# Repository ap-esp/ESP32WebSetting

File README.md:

# Proyecto: ESP32WebSetting

_(Servidor web) administra el ESP32 DeviceIoT_

## Documentación en general

* [Url de Udemy](https://www.udemy.com/course/esp32websetting/learn/lecture/38215070?start=15#content) - Para acceder al curso de Udemy _Tener en cuenta que se necesitan **credenciales**
* [Instalaciones necesarias/recomendadas para el curso](./primeras_secciones/doc/Instalaciones+necesarias+y+complementarias.txt)- *Archivo descargado del curso*

### Enlaces de youtube

*[Primer vìdeo](URL)- *Descripción*  
*[Primer vìdeo](URL)- *Descripción*  
*[Primer vìdeo](URL)- *Descripción*  
*[Primer vìdeo](URL)- *Descripción*  
*[Primer vìdeo](URL)- *Descripción*  
*[Primer vìdeo](URL)- *Descripción*  
*[Primer vìdeo](URL)- *Descripción*  

## Comenzando 🚀

_Estas instrucciones te permitirán obtener una copia del proyecto en funcionamiento en tu máquina local para propósitos de desarrollo y pruebas._

Mira **Deployment** para conocer como desplegar el proyecto.

### Pre-requisitos 📋

* [Hardware](https://www.youtube.com/watch?v=RRcEQ5YeemU) Tutorial de cómo generar el archivo BOM desde KiCAD para realizar los PCB en JLCPCB
* [Caja plàstica](https://es.aliexpress.com/item/1005004092665115.html?spm=a2g0o.order_list.order_list_main.31.6dd5194d1SaNCY&gatewayAdapt=glo2esp) Caja de proyecto electrónico de Riel din, caja de conexiones de plástico ABS de 115x90x40mm, carcasa para PCB.
* [DIAGRAMA ESP32 DEVKIT](./primeras_secciones/doc/DIAGRAMA+ESP32+DEVKIT.pptx) Esquema bàsico de conexiones
* [Esquema y proyecto en KidCad](/home/arch/Escritorio/2024/ESP/ap-esp/ESP32WebSetting/primeras_secciones/doc/esp32_pro_relay/) Toda la informción y acrhivos del proyecto de **KidCAD**

### Instalación 🔧

_Una serie de ejemplos paso a paso que te dice lo que debes ejecutar para tener un entorno de desarrollo ejecutandose_

_Dí cómo será ese paso_

```
Da un ejemplo
```

_Y repite_

```
hasta finalizar
```

_Finaliza con un ejemplo de cómo obtener datos del sistema o como usarlos para una pequeña demo_

## Ejecutando las pruebas ⚙️

_Explica como ejecutar las pruebas automatizadas para este sistema_

### Analice las pruebas end-to-end 🔩

_Explica que verifican estas pruebas y por qué_

```
Da un ejemplo
```

### Y las pruebas de estilo de codificación ⌨️

_Explica que verifican estas pruebas y por qué_

```
Da un ejemplo
```

## Despliegue 📦

_Agrega notas adicionales sobre como hacer deploy_

## Construido con 🛠️

Herramientas que se utilizaron  para crear el proyecto_

* [Platformio.io](https://platformio.org/) _FrameWork/plugins en VSC_

<!-- * [Maven](https://maven.apache.org/) - Manejador de dependencias -->

---

## Estrucutura general del proyecto:

### [Sección 1](https://www.udemy.com/course/esp32websetting/learn/lecture/36962890#overview) *Introducción*

### [Sección 2](https://www.udemy.com/course/esp32websetting/learn/lecture/36964390#overview) *Proyecto que vamos a realizar*

### [Sección 3](https://www.udemy.com/course/esp32websetting/learn/lecture/37001740#overview) *Harware y su esquema en KidCAD*

### [Sección 4](https://www.udemy.com/course/esp32websetting/learn/lecture/37020782#overview) *Conceptos generales de MQTT*

### [Sección 5](https://www.udemy.com/course/esp32websetting/learn/lecture/37086464#overview) *Instalación del Bróker EMQX en docker*

### [Sección 6](https://www.udemy.com/course/esp32websetting/learn/lecture/37121166#overview) *Estructura HTML del proyecto*

### [Sección 7](https://www.udemy.com/course/esp32websetting/learn/lecture/37155996#overview) *Incio del proyecto en Platformio*

### [Sección 8](https://www.udemy.com/course/esp32websetting/learn/lecture/37223820#overview) *API REST del proyecto*

### [Sección 9](https://www.udemy.com/course/esp32websetting/learn/lecture/37165056#overview) *Conceptos bàsicos de JS*

### [Sección 10](https://www.udemy.com/course/esp32websetting/learn/lecture/37412158#overview) *Desarrollo del FrontEnd*

### [Sección 11](https://www.udemy.com/course/esp32websetting/learn/lecture/37577318#overview) *Herramientas para optimizar el proyecto antes de subir el código al ESP*

### [Sección 12](https://www.udemy.com/course/esp32websetting/learn/lecture/37678032#overview) *Preparación del código para el pasaje a producción*

### [Sección 13](https://www.udemy.com/course/esp32websetting/learn/lecture/38093028#overview) *Actualizaciones generales en MQTT*

### [Sección 14](https://www.udemy.com/course/esp32websetting/learn/lecture/38215070#overview) *Recomendaciones y contenidos extras*

## Licencia 📄

---

Este proyecto está bajo la Licencia (Tu Licencia) - mira el archivo [LICENSE.md](LICENSE.md) para detalles
---------------------------------------------------------------------------------------------

## Documentaciones en General🎁

* [CheatSheet general de MD](https://markdown.es/sintaxis-markdown/)
* [Plantilla de documentación](https://gist.github.com/Villanuevand/6386899f70346d4580c723232524d35a) Villanuevand/README-español.md
* etc.

---

## Versionado 📌

Usamos [SemVer](http://semver.org/) para el versionado. Para todas las versiones disponibles, mira los [tags en este repositorio](https://github.com/tu/proyecto/tags).

## Autores ✒️

_Quienes estan involucrados y ayudaron a levantar el proyecto desde sus inicios_

* **Alejandro Palestrini** - *Trabajo Inicial* - [apalestrini](https://github.com/apalestrini)
* **Walter Fernandez** - *Consultor externo, referente, cliente* - [Email de Walter](mailto:astorfernandez@gmail.com)

⌨️ con ❤️ por [apalestrini](https://github.com/apalestrini) 😊

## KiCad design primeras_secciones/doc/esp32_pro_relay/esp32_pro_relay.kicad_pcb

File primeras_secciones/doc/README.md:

# Introducciòn al curso ESP32 de UDEMY, URL:
https://www.udemy.com/course/esp32websetting/learn/lecture/36962890#overview

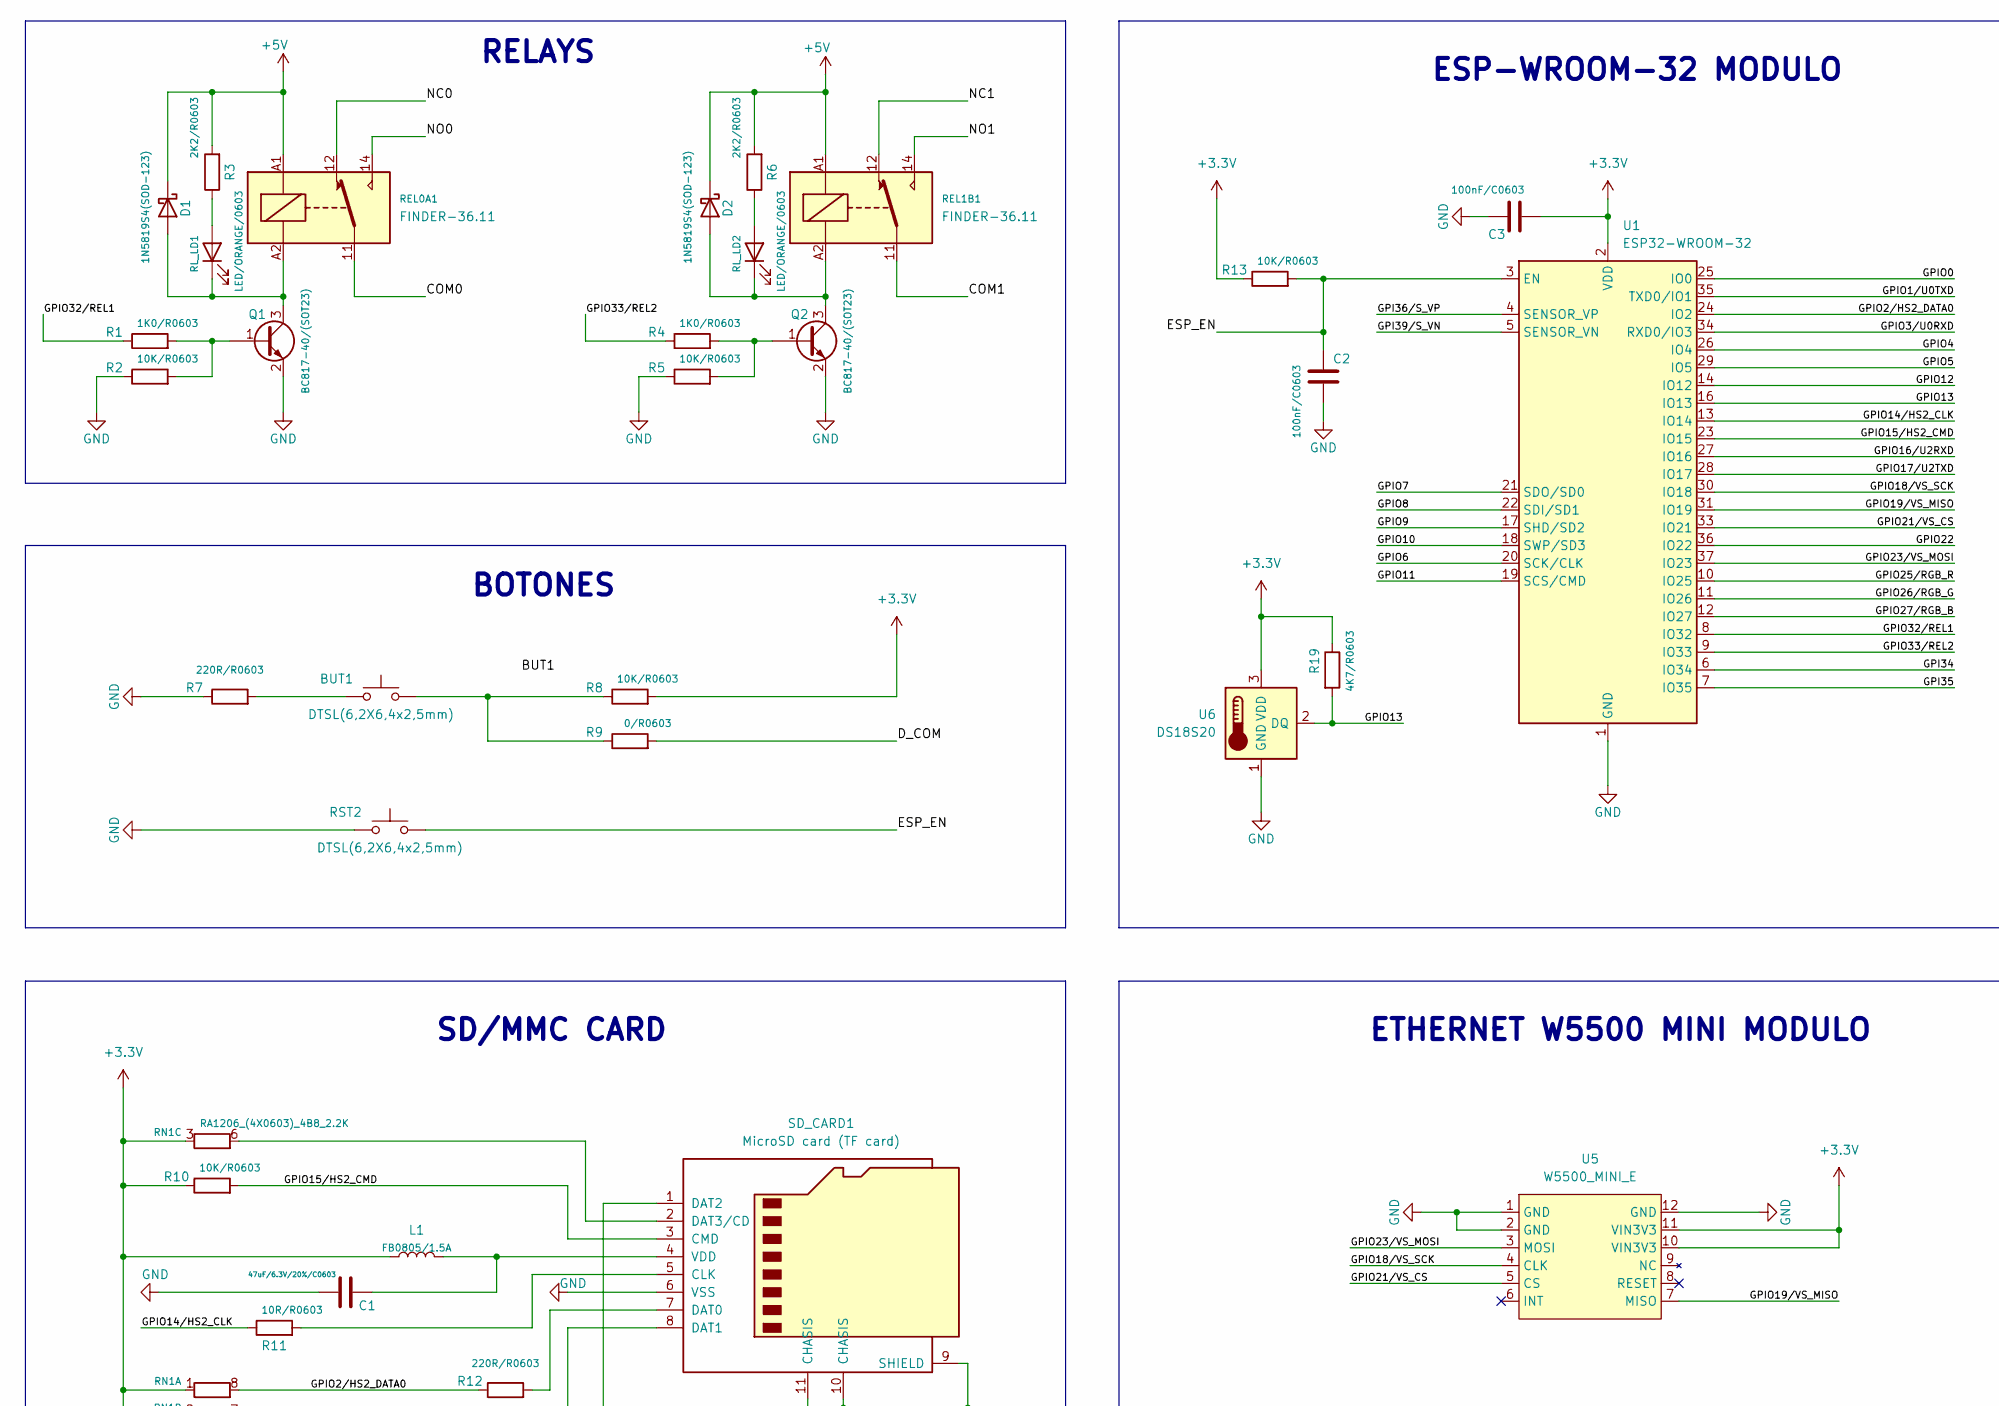
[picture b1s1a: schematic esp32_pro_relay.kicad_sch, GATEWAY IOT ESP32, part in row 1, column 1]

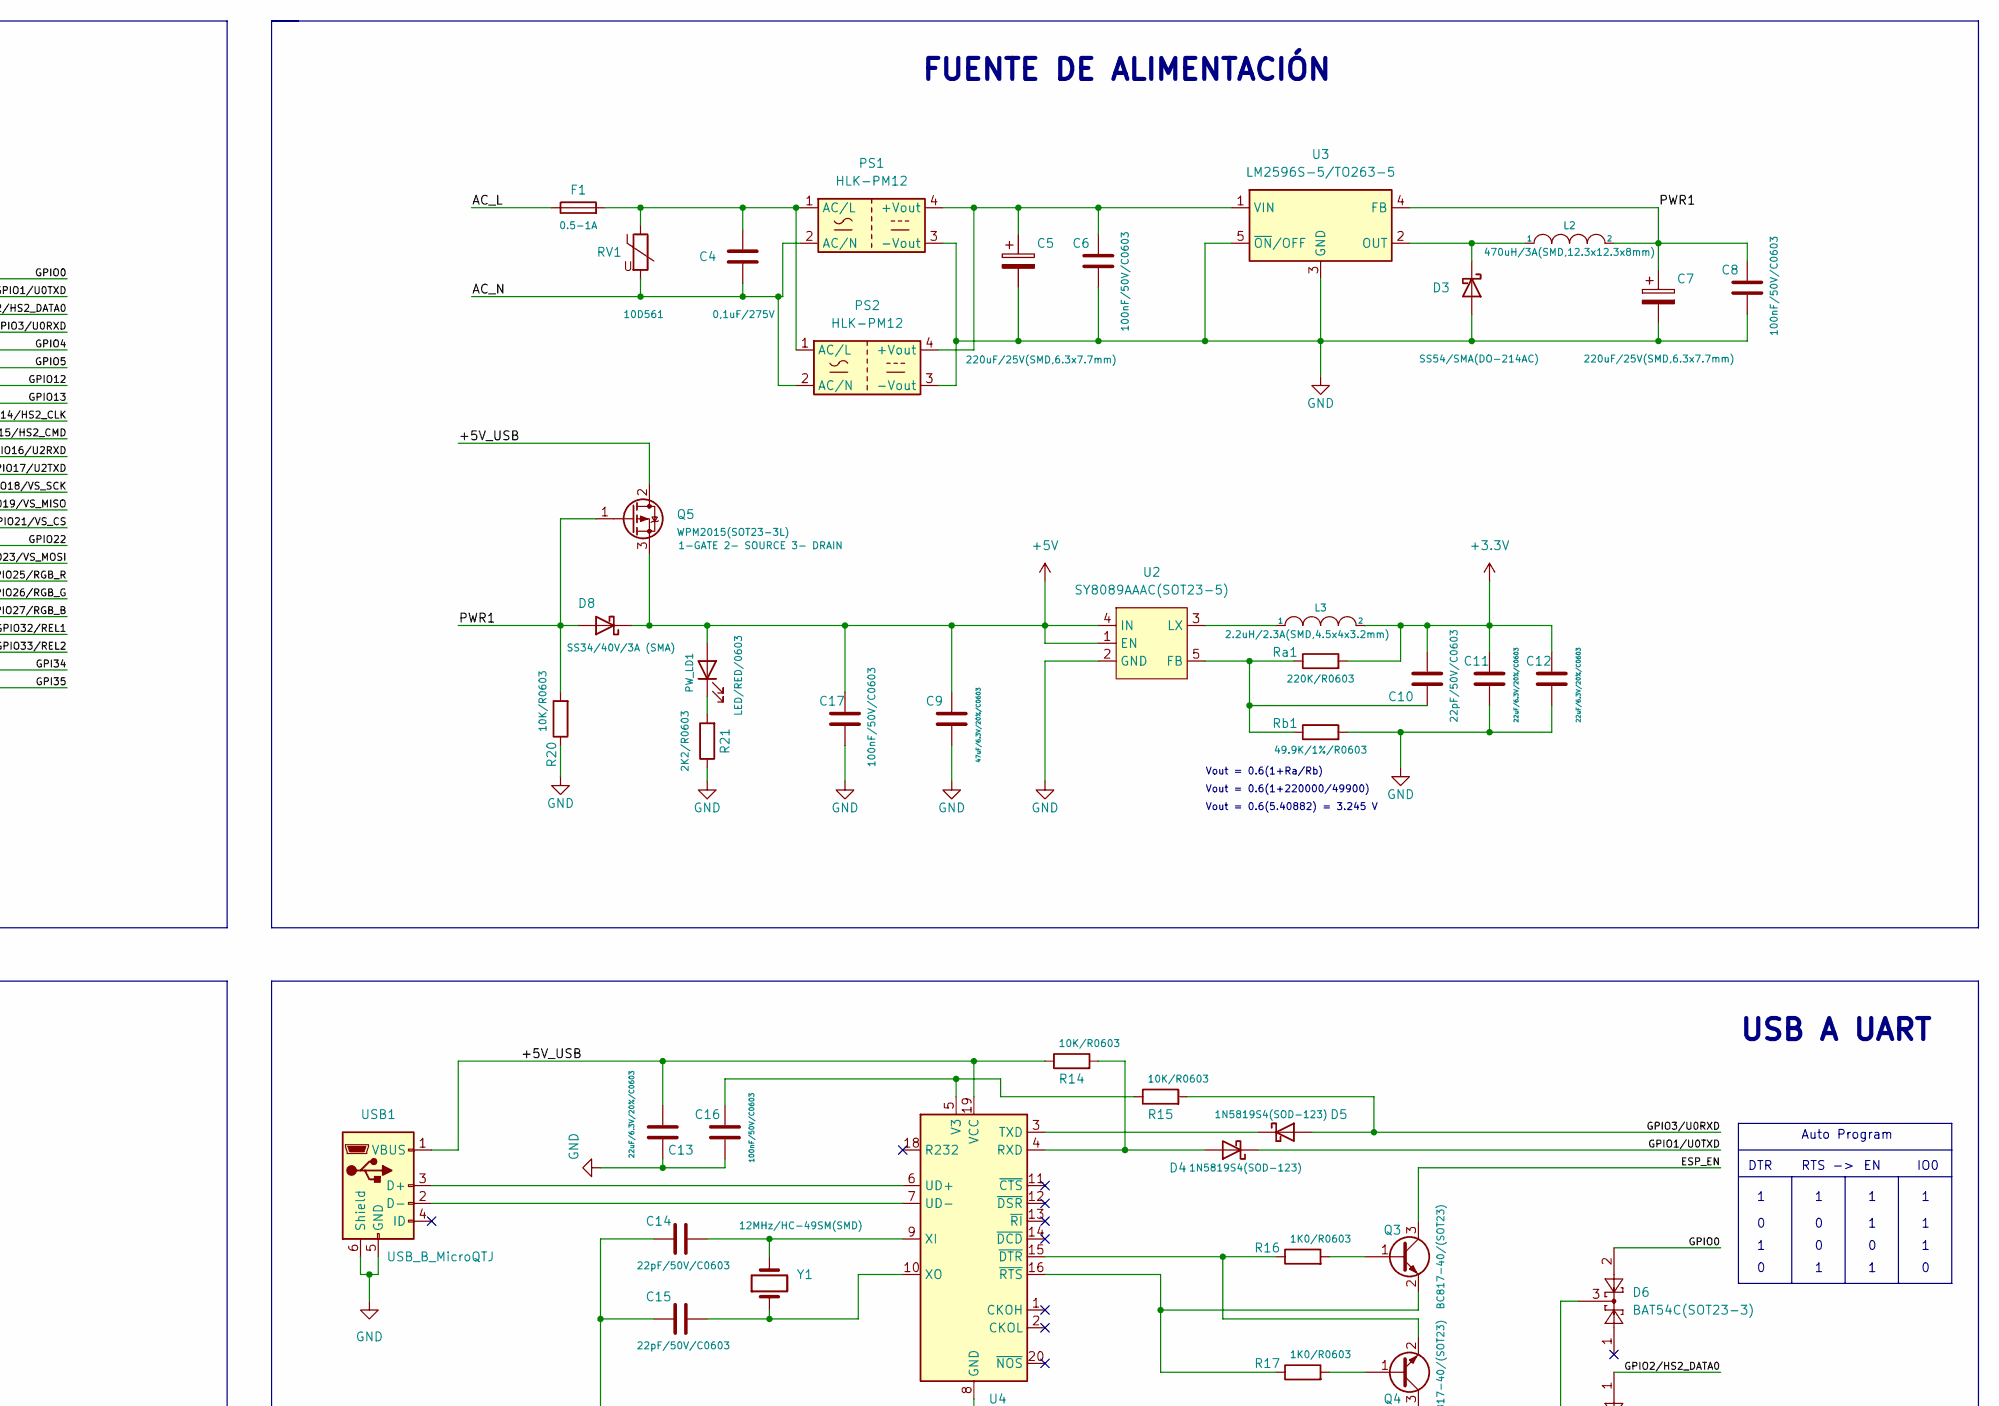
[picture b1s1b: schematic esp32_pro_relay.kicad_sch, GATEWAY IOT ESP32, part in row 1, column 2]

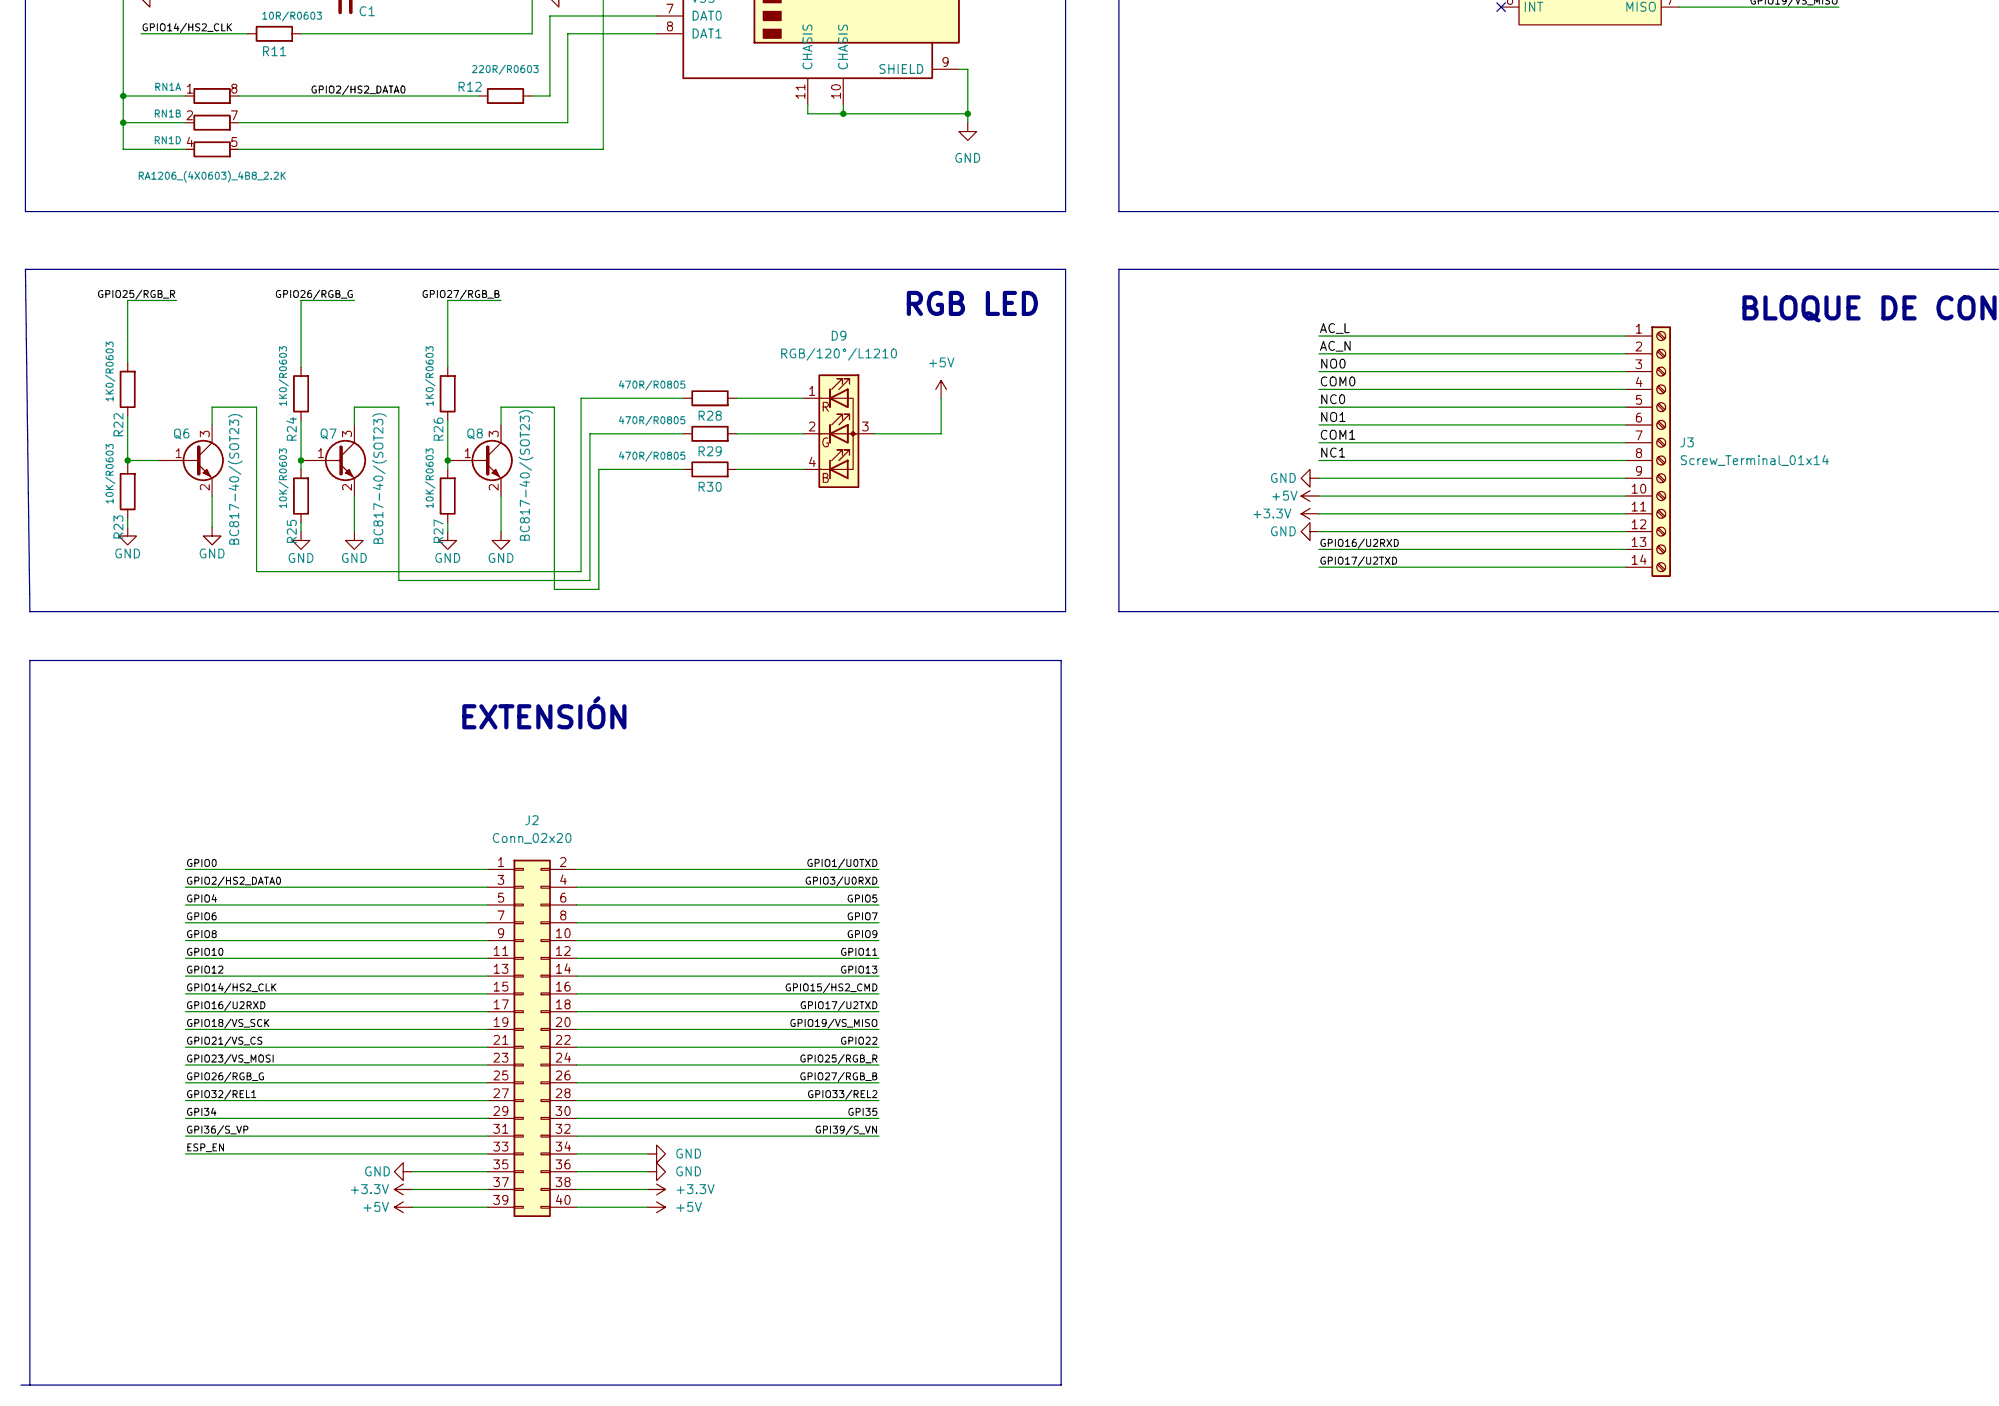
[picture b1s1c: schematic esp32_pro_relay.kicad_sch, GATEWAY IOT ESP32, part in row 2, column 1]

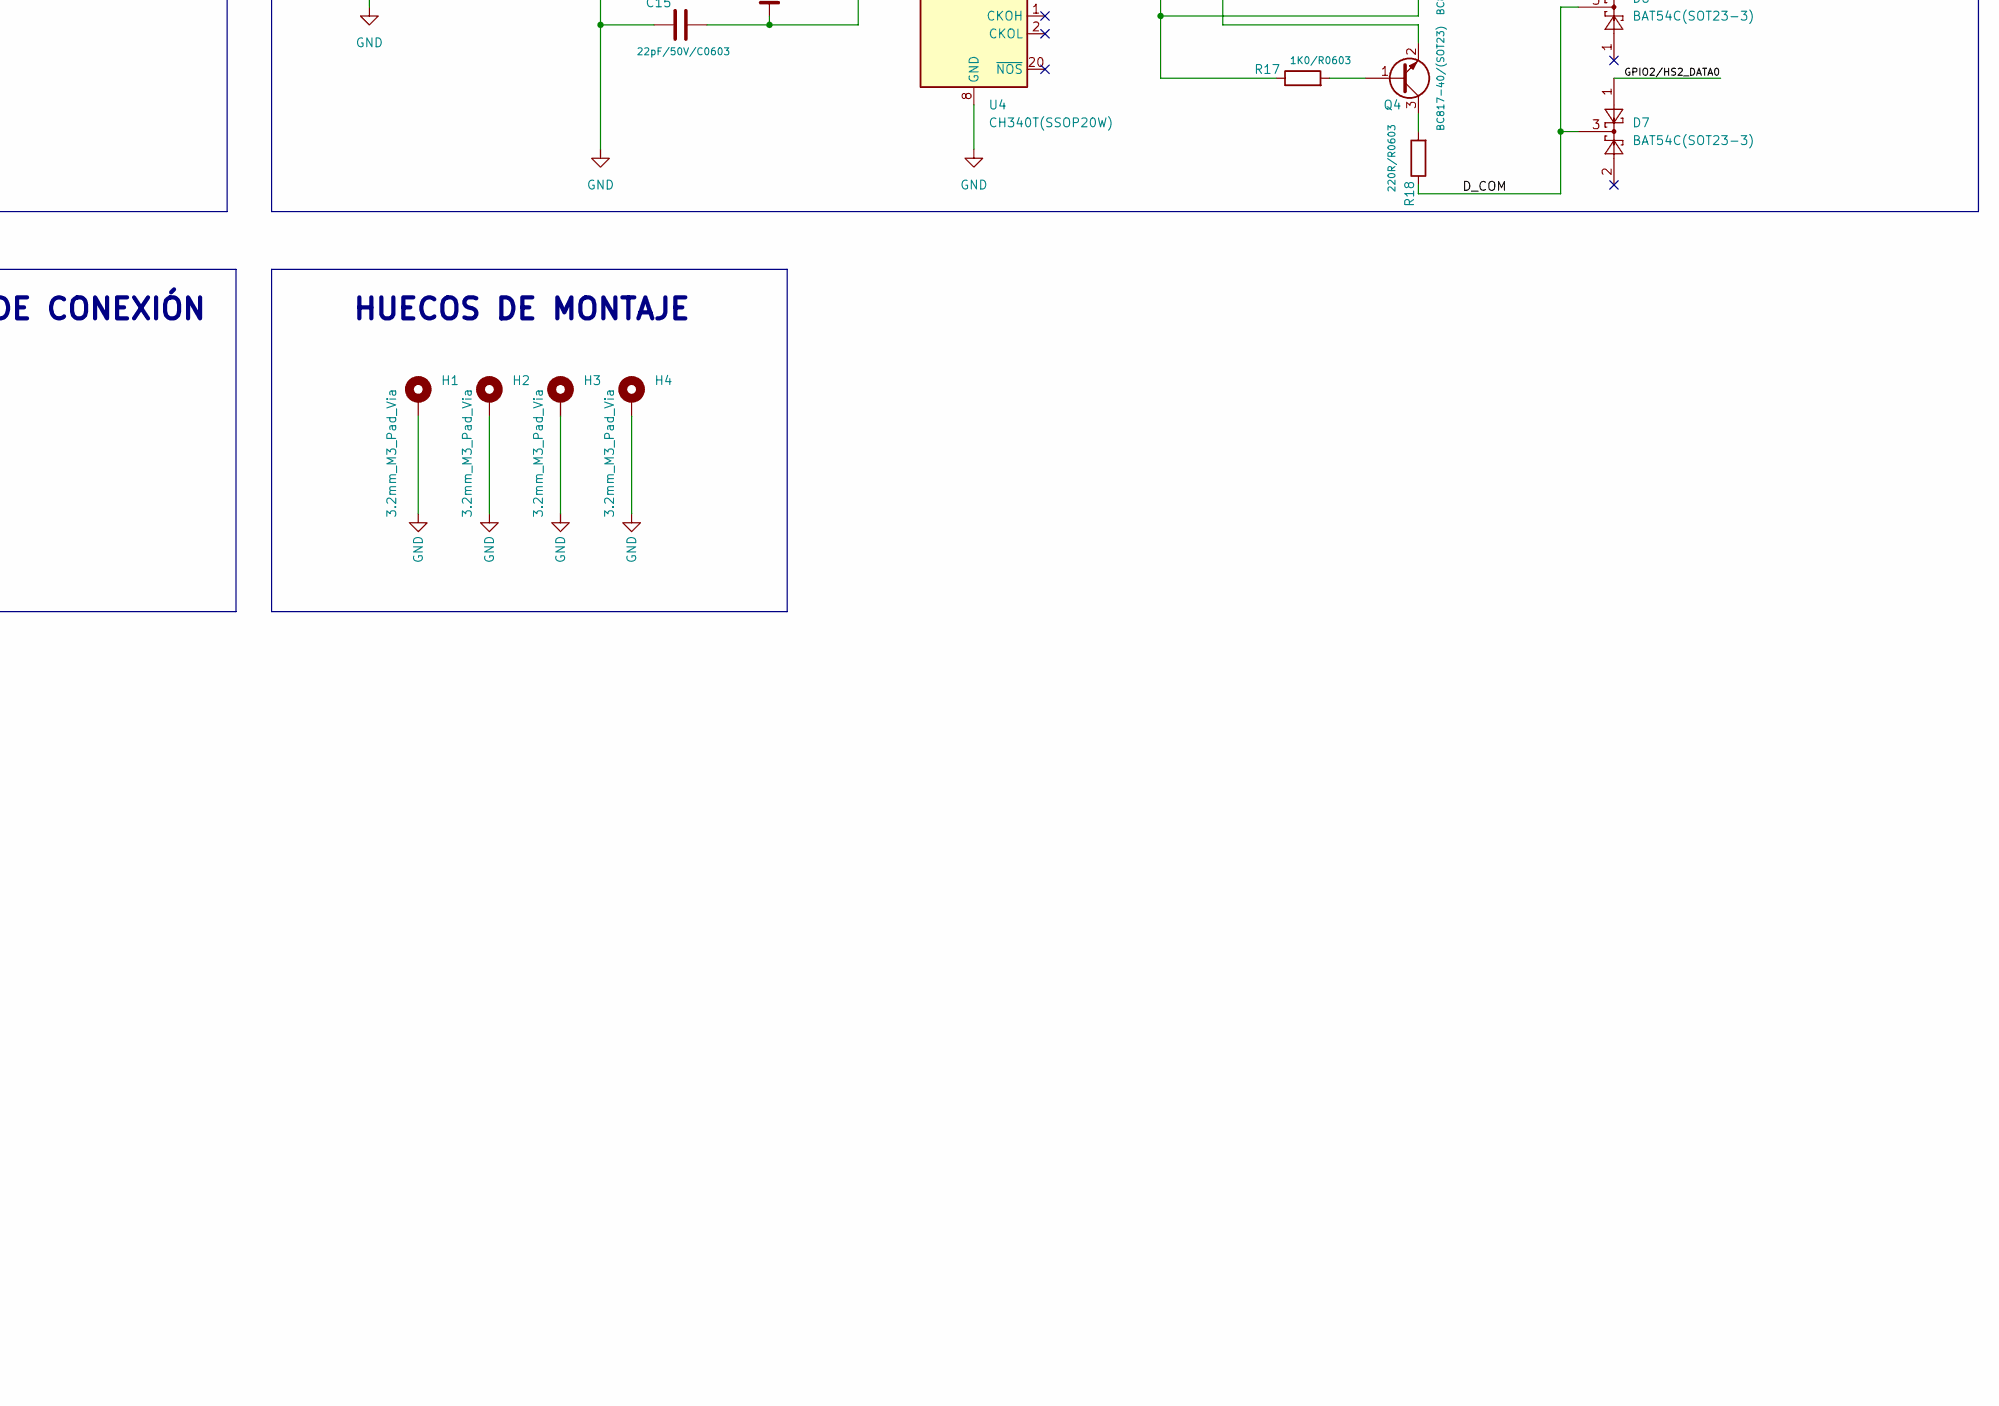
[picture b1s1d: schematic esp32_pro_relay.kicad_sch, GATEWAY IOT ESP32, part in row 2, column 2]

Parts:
BUT1: DTSL(6,2X6,4x2,5mm); SW_Push_1P1T_NO_CK_KSC6xxJ; Mfr.Part # DTSL-61N-V-T/R; LCSC C495902
C1, C9: 47uF/6.3V/20%/C0603; C_0603_1608Metric; Mfr.Part # GRM188R60J476ME15D; LCSC C140782
C2, C3: 100nF/C0603; C_0603_1608Metric; LCSC C14663
C4: 0,1uF/275V; C_Disc_D10.5mm_W5.0mm_P10.00mm
C5, C7: 220uF/25V(SMD,6.3x7.7mm); CP_Elec_6.3x7.7; Mfr.Part # RVT1E221M0607; LCSC C696188
C6, C8, C16, C17: 100nF/50V/C0603; C_0603_1608Metric; Mfr.Part # CC0603KRX7R9BB104; LCSC C14663
C10, C14, C15: 22pF/50V/C0603; C_0603_1608Metric; Mfr.Part # CC0603JRNPO9BN220; LCSC C105620
C11, C12, C13: 22uF/6.3V/20%/C0603; C_0603_1608Metric; Mfr.Part # CC0603MRX5R5BB226; LCSC C109448
D1, D2, D4, D5: 1N5819S4(SOD-123); D_SOD-123; Mfr.Part 1N5819W; LCSC C963381
D3: SS54/SMA(DO-214AC); D_SMA; Mfr.Part # SS54A; LCSC C2827918
D6, D7: BAT54C(SOT23-3); SOT-23; Mfr.Part # BAT54C,215; LCSC C37704
D8: SS34/40V/3A (SMA); D_SMA; Mfr.Part # SS34; LCSC C408258
D9: RGB/120°/L1210; LED_RGB_1210; Mfr.Part # XL-3227RGB-RF; LCSC C965844
F1: 0.5-1A; Fuseholder_Littelfuse_445_030_series_5x20mm
H1, H2, H3, H4: 3.2mm_M3_Pad_Via; MountingHole_2.7mm_Pad_Via
J2: Conn_02x20; PinHeader_2x20_P2.54mm_Vertical
J3: Screw_Terminal_01x14; TerminalBlock_Phoenix_PT-1,5-14-5.0-H_1x14_P5.00mm_Horizont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
L1: FB0805/1.5A; L_0805_2012Metric; Mfr.Part # LQM21PN1R0MGHL; LCSC C343191
L2: 470uH/3A(SMD,12.3x12.3x8mm); L_12x12mm_H8mm; Mfr.Part # CYH127-33UH; LCSC C2929502
L3: 2.2uH/2.3A(SMD,4.5x4x3.2mm); L_Bourns-SRN4018; Mfr.Part # CY43-2.2UH; LCSC C2929416
PS1: HLK-PM12; CONV_HLK-5M05
PS2: HLK-PM12; Converter_ACDC_HiLink_HLK-PMxx
PW_LD1: LED/RED/0603; LED_0603_1608Metric; Mfr.Part # SZYY0603R; LCSC C434419
Q1, Q2, Q3, Q4, Q6, Q7, Q8: BC817-40/(SOT23); SOT-23; Mfr.Part # BC817-40,215; LCSC C52801
Q5: WPM2015(SOT23-3L); SOT-23; Mfr.Part WPM2015-MS; LCSC C2830124
R1, R4, R16, R17, R22, R24, R26: 1K0/R0603; R_0603_1608Metric; Mfr.Part # RC0603FR-071KL; LCSC C22548
R2, R5, R8, R10, R13, R14, R15, R23, R25, R27: 10K/R0603; R_0603_1608Metric; Mfr.Part RC0603JR-0710KL; LCSC C2930027
R3, R6, R21: 2K2/R0603; R_0603_1608Metric; Mfr.Part # RC0603JR-072K2L; LCSC C113303
R7, R12, R18: 220R/R0603; R_0603_1608Metric; Mfr.Part # RC0603JR-07220RL; LCSC C114683
R9: 0/R0603; R_0603_1608Metric
R11: 10R/R0603; R_0603_1608Metric; Mfr.Part # RC0603FR-0710RL; LCSC C109318
R19: 4K7/R0603; R_0603_1608Metric; Mfr.Part RC0603JR-0710KL; LCSC C2930027
R20: 10K/R0603; R_0603_1608Metric; Mfr.Part RC0603JR-0710KL; LCSC C99198
R28, R29, R30: 470R/R0805; R_0805_2012Metric; Mfr.Part # RC0603FR-07470RL; LCSC C114669
REL0A1, REL1B1: FINDER-36.11; Relay_SPDT_Finder_36.11
RL_LD1, RL_LD2: LED/ORANGE/0603; LED_0603_1608Metric; Mfr.Part # SZYY0603O; LCSC C434425
RN1: RA1206_(4X0603)_4B8_2.2K; R_Array_Convex_4x0603; Mfr.Part YC164-JR-072K2L; LCSC C136829
RST2: DTSL(6,2X6,4x2,5mm); SW_Push_1P1T_NO_CK_KSC6xxJ; Mfr.Part # DTSL-61N-V-T/R; LCSC C495902
RV1: 10D561; RV_Disc_D9mm_W5.2mm_P5mm
Ra1: 220K/R0603; R_0603_1608Metric; Mfr.Part # AC0603JR-07220KL; LCSC C228160
Rb1: 49.9K/1%/R0603; R_0603_1608Metric; Mfr.Part # RC0603FR-0749K9L; LCSC C114624
SD_CARD1: MicroSD card (TF card); microSD_HC_Molex_104031-0811; Mfr.Part 1040310811; LCSC C585350
U1: ESP32-WROOM-32; Mfr.Part # ESP32-WROOM-32; LCSC C82899
U2: SY8089AAAC(SOT23-5); SOT-23-5; Mfr.Part SY8089AAAC; LCSC C78988
U3: LM2596S-5/TO263-5; TO-263-5_TabPin3; Mfr.Part # LM2596S-5.0/TR; LCSC C194349
U4: CH340T(SSOP20W); SSOP-20_5.3x7.2mm_P0.65mm; Mfr.Part CH340T; LCSC C8689
U5: W5500_MINI_E; W5500_mini
U6: DS18S20; TO-92_HandSolder
USB1: USB_B_MicroQTJ; USB_Micro-B_Molex-105017-0001; Mfr.Part 1050170001; LCSC C136000
Y1: 12MHz/HC-49SM(SMD); Crystal_SMD_HC49-SD; Mfr.Part # X49SM12MSD2SC; LCSC C14871

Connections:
+3.3V: C3.2, C10.1, C11.1, C12.1, J2.37, J2.38, J3.11, L1.1, L3.2, R8.2, R10.1, R13.1, R19.1, RN1.1 (R1.1), RN1.2 (R2.1), RN1.3 (R3.1), RN1.4 (R4.1), Ra1.2, U1.2 (VDD), U5.10 (VIN3V3), U5.11 (VIN3V3), U6.3 (VDD)
+5V: C9.1, C17.1, D1.1 (K), D2.1 (K), D8.1 (K), D9.3 (A), J2.39, J2.40, J3.10, PW_LD1.2 (A), Q5.3 (S), R3.2, R6.2, REL0A1.A1, REL1B1.A1, U2.1 (EN), U2.4 (IN)
/+5V_USB: C13.1, Q5.2 (D), R14.1, U4.19 (VCC), USB1.1 (VBUS)
/AC_L: F1.1, J3.1
/AC_N: C4.2, J3.2, PS1.2 (AC/N), PS2.2 (AC/N), RV1.2
/COM0: J3.4, REL0A1.11
/COM1: J3.7, REL1B1.11
/D_COM: D6.3, D7.3, R9.2, R18.1
/ESP_EN: C2.1, J2.33, Q3.3 (C), R13.2, RST2.2, U1.3 (EN)
/GPI34: J2.29, U1.6 (IO34)
/GPI35: J2.30, U1.7 (IO35)
/GPI36/S_VP: J2.31, U1.4 (SENSOR_VP)
/GPI39/S_VN: J2.32, U1.5 (SENSOR_VN)
/GPIO0: D6.2, J2.1, U1.25 (IO0)
/GPIO1/U0TXD: D4.1 (K), J2.2, U1.35 (TXD0/IO1)
/GPIO2/HS2_DATA0: D7.1, J2.3, R12.1, RN1.8 (R1.2), U1.24 (IO2)
/GPIO3/U0RXD: D5.2 (A), J2.4, R15.2, U1.34 (RXD0/IO3)
/GPIO4: J2.5, U1.26 (IO4)
/GPIO5: J2.6, U1.29 (IO5)
/GPIO6: J2.7, U1.20 (SCK/CLK)
/GPIO7: J2.8, U1.21 (SDO/SD0)
/GPIO8: J2.9, U1.22 (SDI/SD1)
/GPIO9: J2.10, U1.17 (SHD/SD2)
/GPIO10: J2.11, U1.18 (SWP/SD3)
/GPIO11: J2.12, U1.19 (SCS/CMD)
/GPIO12: J2.13, U1.14 (IO12)
/GPIO13: J2.14, R19.2, U1.16 (IO13), U6.2 (DQ)
/GPIO14/HS2_CLK: J2.15, R11.1, U1.13 (IO14)
/GPIO15/HS2_CMD: J2.16, R10.2, SD_CARD1.3 (CMD), U1.23 (IO15)
/GPIO16/U2RXD: J2.17, J3.13, U1.27 (IO16)
/GPIO17/U2TXD: J2.18, J3.14, U1.28 (IO17)
/GPIO18/VS_SCK: J2.19, U1.30 (IO18), U5.4 (CLK)
/GPIO19/VS_MISO: J2.20, U1.31 (IO19), U5.7 (MISO)
/GPIO21/VS_CS: J2.21, U1.33 (IO21), U5.5 (CS)
/GPIO22: J2.22, U1.36 (IO22)
/GPIO23/VS_MOSI: J2.23, U1.37 (IO23), U5.3 (MOSI)
/GPIO25/RGB_R: J2.24, R22.2, U1.10 (IO25)
/GPIO26/RGB_G: J2.25, R24.2, U1.11 (IO26)
/GPIO27/RGB_B: J2.26, R26.2, U1.12 (IO27)
/GPIO32/REL1: J2.27, R1.1, U1.8 (IO32)
/GPIO33/REL2: J2.28, R4.1, U1.9 (IO33)
/NC0: J3.5, REL0A1.12
/NC1: J3.8, REL1B1.12
/NO0: J3.3, REL0A1.14
/NO1: J3.6, REL1B1.14
/PWR1: C7.1, C8.1, D8.2 (A), L2.2, Q5.1 (G), R20.2, U3.4 (FB)
GND: C1.1, C2.2, C3.1, C5.2, C6.2, C7.2, C8.2, C9.2, C11.2, C12.2, C13.2, C14.2, C15.2, C16.2, C17.2, D3.2 (A), H1.1, H2.1, H3.1, H4.1, J2.34, J2.35, J2.36, J3.9, J3.12, PS1.3 (-Vout), PS2.3 (-Vout), Q1.2 (E), Q2.2 (E), Q6.2 (E), Q7.2 (E), Q8.2 (E), R2.1, R5.1, R7.1, R20.1, R21.1, R23.1, R25.1, R27.1, RST2.1, Rb1.2, SD_CARD1.6 (VSS), SD_CARD1.9 (SHIELD), SD_CARD1.10 (CHASIS), SD_CARD1.11 (CHASIS), U1.1 (GND), U1.15 (GND), U1.38 (GND), U1.39 (GND), U2.2 (GND), U3.3 (GND), U3.5 (~ON/OFF), U4.8 (GND), U5.1 (GND), U5.2 (GND), U5.12 (GND), U6.1 (GND), USB1.5 (GND), USB1.6 (Shield)
unnamed: BUT1.1, R7.2
unnamed: BUT1.2, R8.1, R9.1
unnamed: C1.2, L1.2, SD_CARD1.4 (VDD)
unnamed: C4.1, F1.2, PS1.1 (AC/L), PS2.1 (AC/L), RV1.1
unnamed: C5.1, C6.1, PS1.4 (+Vout), PS2.4 (+Vout), U3.1 (VIN)
unnamed: C10.2, Ra1.1, Rb1.1, U2.5 (FB)
unnamed: C14.1, U4.9 (XI), Y1.2
unnamed: C15.1, U4.10 (XO), Y1.1
unnamed: C16.1, R15.1, U4.5 (V3)
unnamed: D1.2 (A), Q1.3 (C), REL0A1.A2, RL_LD1.1 (K)
unnamed: D2.2 (A), Q2.3 (C), REL1B1.A2, RL_LD2.1 (K)
unnamed: D3.1 (K), L2.1, U3.2 (OUT)
unnamed: D4.2 (A), R14.2, U4.4 (RXD)
unnamed: D5.1 (K), U4.3 (TXD)
unnamed: D9.1 (RK), R28.2
unnamed: D9.2 (GK), R29.2
unnamed: D9.4 (BK), R30.2
unnamed: L3.1, U2.3 (LX)
unnamed: PW_LD1.1 (K), R21.2
unnamed: Q1.1 (B), R1.2, R2.2
unnamed: Q2.1 (B), R4.2, R5.2
unnamed: Q3.1 (B), R16.2
unnamed: Q3.2 (E), R17.1, U4.16 (~RTS)
unnamed: Q4.1 (B), R17.2
unnamed: Q4.2 (E), R16.1, U4.15 (~DTR)
unnamed: Q4.3 (C), R18.2
unnamed: Q6.1 (B), R22.1, R23.2
unnamed: Q6.3 (C), R28.1
unnamed: Q7.1 (B), R24.1, R25.2
unnamed: Q7.3 (C), R29.1
unnamed: Q8.1 (B), R26.1, R27.2
unnamed: Q8.3 (C), R30.1
unnamed: R3.1, RL_LD1.2 (A)
unnamed: R6.1, RL_LD2.2 (A)
unnamed: R11.2, SD_CARD1.5 (CLK)
unnamed: R12.2, SD_CARD1.7 (DAT0)
unnamed: RN1.5 (R4.2), SD_CARD1.1 (DAT2)
unnamed: RN1.6 (R3.2), SD_CARD1.2 (DAT3/CD)
unnamed: RN1.7 (R2.2), SD_CARD1.8 (DAT1)
unnamed: U4.6 (UD+), USB1.3 (D+)
unnamed: U4.7 (UD-), USB1.2 (D-)

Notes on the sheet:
DTR
RTS
BLOQUE DE CONEXIÓN
SD/MMC CARD
Vout = 0.6(1+220000/49900)
IO0
EXTENSIÓN
BOTONES
ETHERNET W5500 MINI MODULO
USB A UART
RELAYS
HUECOS DE MONTAJE
Vout = 0.6(5.40882) = 3.245 V
Auto Program
ESP-WROOM-32 MODULO
FUENTE DE ALIMENTACIÓN
Vout = 0.6(1+Ra/Rb)
RGB LED

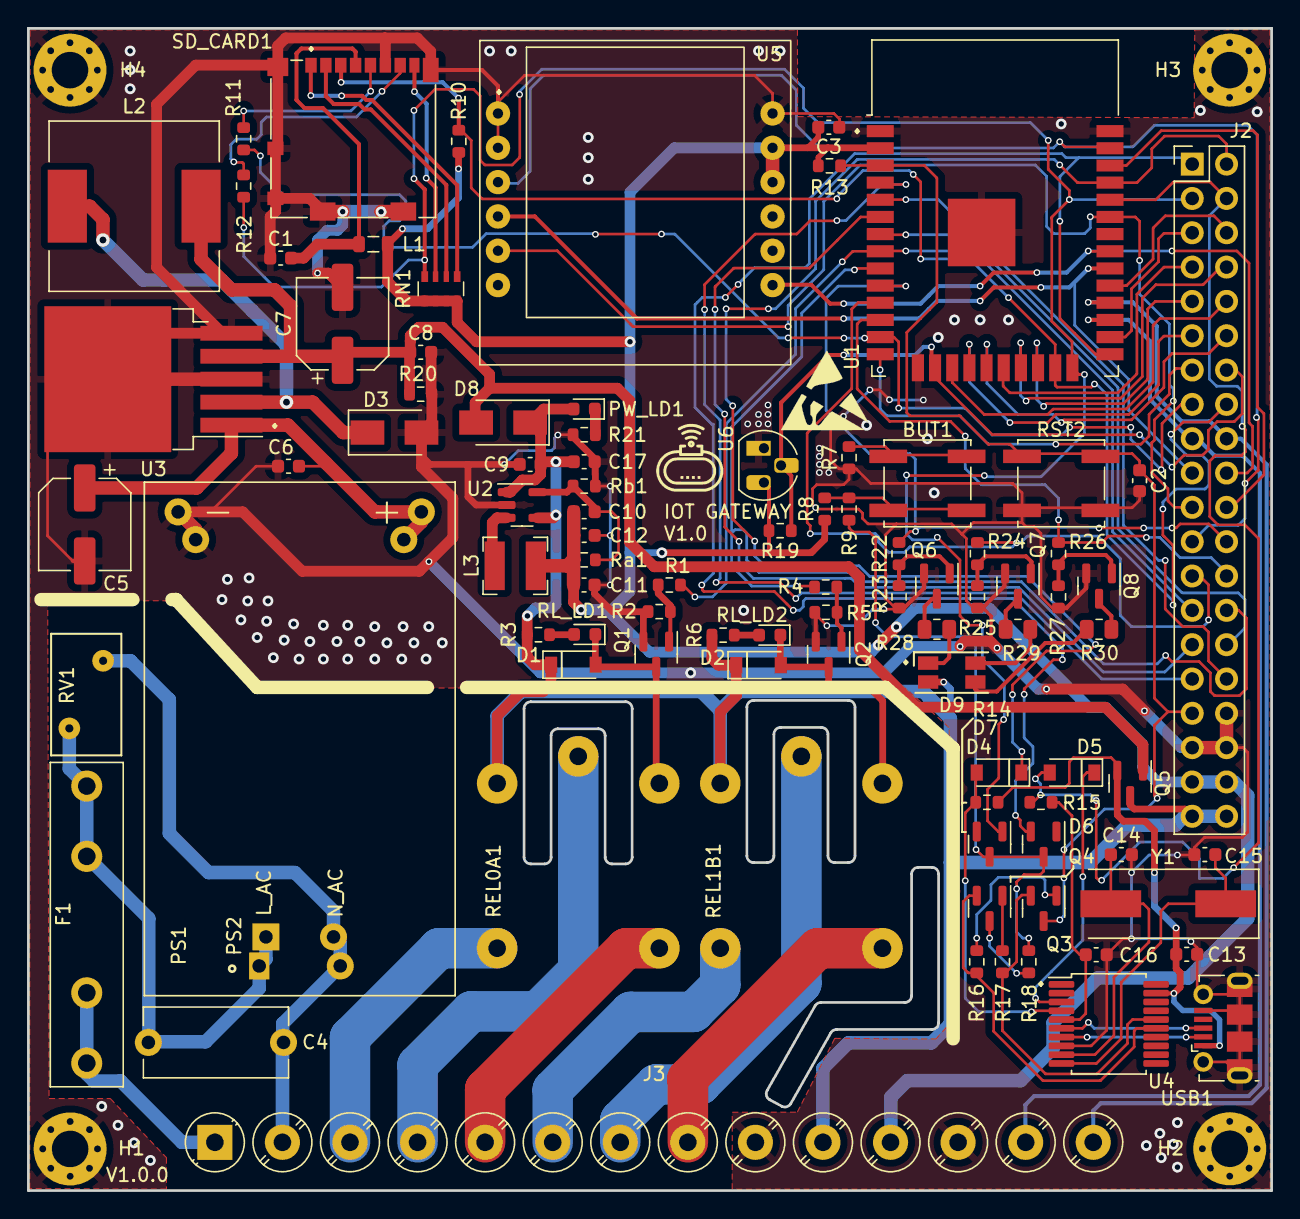
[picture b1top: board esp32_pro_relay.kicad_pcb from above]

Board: 2 copper layers, 92.0 x 86.0 mm, 97 parts (0 on the bottom side), 88 nets.

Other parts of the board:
V1.0.0: cut_92x86_new

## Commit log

2024-01-14 primer commit del proyecto de udemy, estructura general
2024-01-14 Commit con la documentaciòn creada, iniciada y plantillada.
2024-01-14 Documentaciòn actualizada, estructura del curso actualizada, referencias bàsicas organizadas y configuradas
